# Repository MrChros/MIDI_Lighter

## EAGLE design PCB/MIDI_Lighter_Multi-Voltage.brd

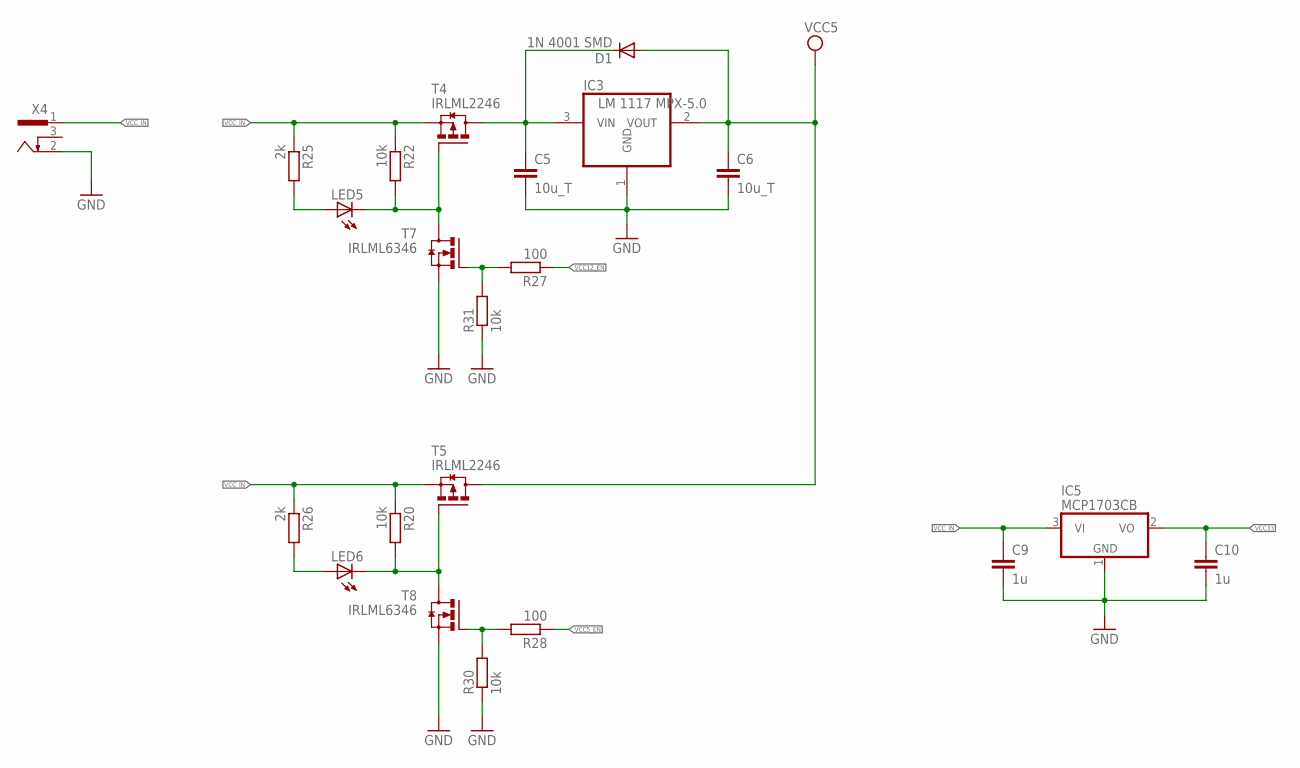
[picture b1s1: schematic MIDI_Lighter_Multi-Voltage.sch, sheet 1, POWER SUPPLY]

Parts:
C5, C6: 10u_T; C1210
C9, C10: 1u; C0805
D1: 1N 4001 SMD; MINIMELF
IC3: LM 1117 MPX-5.0; SOT223
IC5: MCP1703CB; SOT23
LED5, LED6: LEDCHIP-LED0805; CHIP-LED0805
R20, R22, R30, R31: 10k; R0805
R25, R26: 2k; R0805
R27, R28: 100; R0805
T4, T5: IRLML2246; SOT23
T7, T8: IRLML6346; SOT23
X4: 733980-62

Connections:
GND: C5.2, C6.2, C9.2, C10.2, IC3.1 (GND), IC5.1 (GND), R30.1, R31.1, T7.2 (S), T8.2 (S), X4.2; also elsewhere on the board
unnamed: C5.1, D1.C, IC3.3 (VIN), T4.3 (D)
unnamed: LED5.C, R22.2, T4.1 (G), T7.3 (D)
unnamed: LED6.C, R20.2, T5.1 (G), T8.3 (D)
unnamed: LED6.A, R26.2
unnamed: LED5.A, R25.2
unnamed: R27.2, R31.2, T7.1 (G)
unnamed: R28.2, R30.2, T8.1 (G)
VCC: C6.1, D1.A, IC3.2 (VOUT), T5.3 (D); also elsewhere on the board
VCC5_EN: R28.1; also elsewhere on the board
VCC12_EN: R27.1; also elsewhere on the board
VCC33: C10.1, IC5.2 (VO); also elsewhere on the board
VCC_IN: C9.1, IC5.3 (VI), R20.1, R22.1, R25.1, R26.1, T4.2 (S), T5.2 (S), X4.1; also elsewhere on the board

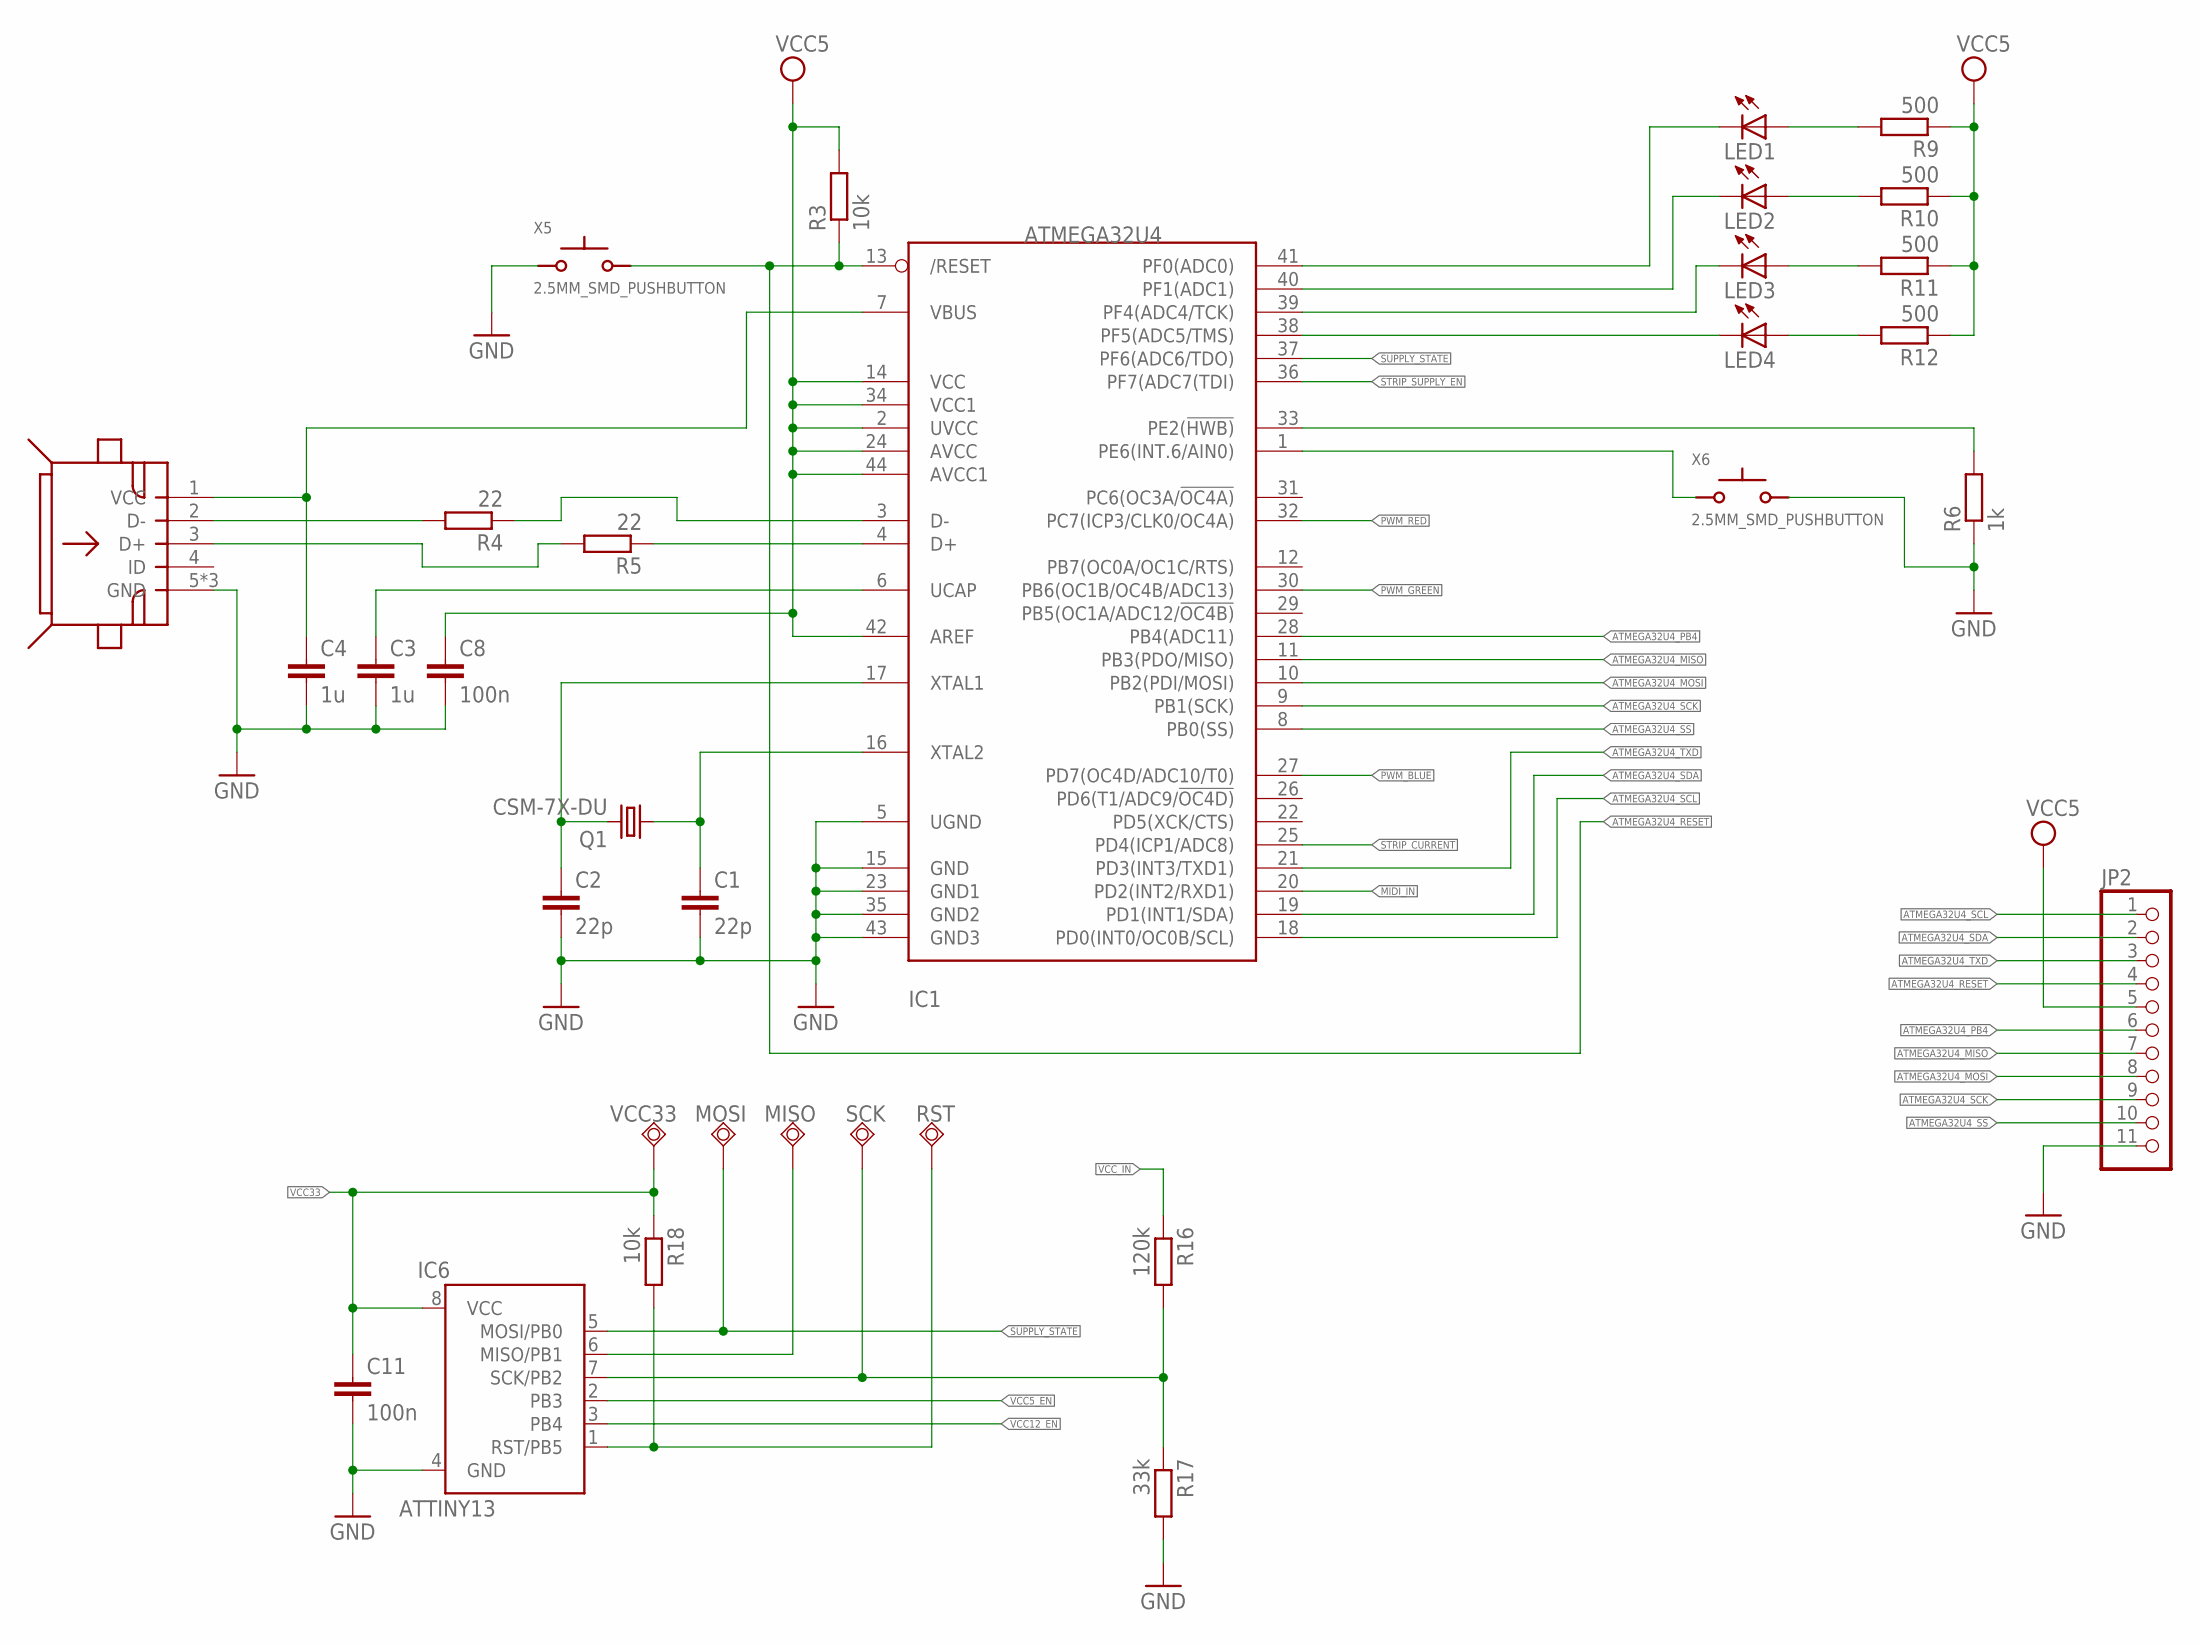
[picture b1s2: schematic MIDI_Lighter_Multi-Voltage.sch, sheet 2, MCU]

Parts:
C1, C2: 22p; C0805
C3, C4: 1u; C0805
C8, C11: 100n; C0805
IC1: ATMEGA32U4; TQFP44
IC6: ATTINY13; SO08
JP2: PINHD-1X11; 1X11
LED1, LED2, LED3, LED4: LEDCHIP-LED0805; CHIP-LED0805
MISO: TPSQTP13R; TP13R
MOSI: TPSQTP13R; TP13R
Q1: CSM-7X-DU
R3, R18: 10k; R0805
R4, R5: 22; R0805
R6: 1k; R0805
R9, R10, R11, R12: 500; R0805
R16: 120k; R0805
R17: 33k; R0805
RST: TPSQTP13R; TP13R
SCK: TPSQTP13R; TP13R
VCC33: TPSQTP13R; TP13R
X3: USB_MICRO_BUCHSE_LCSC
X5, X6: 2.5MM_SMD_PUSHBUTTON

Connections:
ATMEGA32U4_MISO: IC1.11 (PB3(PDO/MISO)), JP2.7
ATMEGA32U4_MOSI: IC1.10 (PB2(PDI/MOSI)), JP2.8; also elsewhere on the board
ATMEGA32U4_PB4: IC1.28 (PB4(ADC11)), JP2.6
ATMEGA32U4_RESET: IC1.13 (/RESET), JP2.4, R3.1, X5.2
ATMEGA32U4_SCK: IC1.9 (PB1(SCK)), JP2.9; also elsewhere on the board
ATMEGA32U4_SCL: IC1.18 (PD0(INT0/OC0B/SCL)), JP2.1
ATMEGA32U4_SDA: IC1.19 (PD1(INT1/SDA)), JP2.2
ATMEGA32U4_SS: IC1.8 (PB0(SS)), JP2.10
ATMEGA32U4_TXD: IC1.21 (PD3(INT3/TXD1)), JP2.3
GND: C1.2, C2.2, C3.2, C4.2, C8.2, C11.2, IC1.5 (UGND), IC1.15 (GND), IC1.23 (GND1), IC1.35 (GND2), IC1.43 (GND3), IC6.4 (GND), JP2.11, R6.1, R17.2, X3.5 (GND), X3.GND1 (GND), X3.GND2 (GND), X5.1, X6.2; also elsewhere on the board
MIDI_IN: IC1.20 (PD2(INT2/RXD1)); also elsewhere on the board
unnamed: R4.2, X3.2 (D-)
unnamed: IC1.3 (D-), R4.1
unnamed: C1.1, IC1.16 (XTAL2), Q1.1
unnamed: C2.1, IC1.17 (XTAL1), Q1.2
unnamed: C3.1, IC1.6 (UCAP)
unnamed: R5.2, X3.3 (D+)
unnamed: IC1.4 (D+), R5.1
unnamed: IC1.33 (PE2(!HWB)), R6.2
unnamed: IC1.41 (PF0(ADC0)), LED1.C
unnamed: IC1.40 (PF1(ADC1)), LED2.C
unnamed: IC1.39 (PF4(ADC4/TCK)), LED3.C
unnamed: IC1.38 (PF5(ADC5/TMS)), LED4.C
unnamed: IC1.1 (PE6(INT.6/AIN0)), X6.1
unnamed: LED1.A, R9.2
unnamed: LED2.A, R10.2
unnamed: LED3.A, R11.2
unnamed: LED4.A, R12.2
unnamed: IC6.1 (RST/PB5), R18.2, RST.TP
unnamed: IC6.6 (MISO/PB1), MISO.TP
PWM_BLUE: IC1.27 (PD7(OC4D/ADC10/T0)); also elsewhere on the board
PWM_GREEN: IC1.30 (PB6(OC1B/OC4B/ADC13)); also elsewhere on the board
PWM_RED: IC1.32 (PC7(ICP3/CLK0/OC4A)); also elsewhere on the board
STRIP_CURRENT: IC1.25 (PD4(ICP1/ADC8)); also elsewhere on the board
STRIP_SUPPLY_EN: IC1.36 (PF7(ADC7(TDI)); also elsewhere on the board
SUPPLY_STATE: IC1.37 (PF6(ADC6/TDO)), IC6.5 (MOSI/PB0), MOSI.TP
VCC: C8.1, IC1.2 (UVCC), IC1.14 (VCC), IC1.24 (AVCC), IC1.34 (VCC1), IC1.42 (AREF), IC1.44 (AVCC1), JP2.5, R3.2, R9.1, R10.1, R11.1, R12.1; also elsewhere on the board
VCC5_EN: IC6.2 (PB3); also elsewhere on the board
VCC12_EN: IC6.3 (PB4); also elsewhere on the board
VCC33: C11.1, IC6.8 (VCC), R18.1, VCC33.TP; also elsewhere on the board
VCC_IN: R16.1; also elsewhere on the board
VCC_USB: C4.1, IC1.7 (VBUS), X3.1 (VCC)
VOLTAGE_READ: IC6.7 (SCK/PB2), R16.2, R17.1, SCK.TP

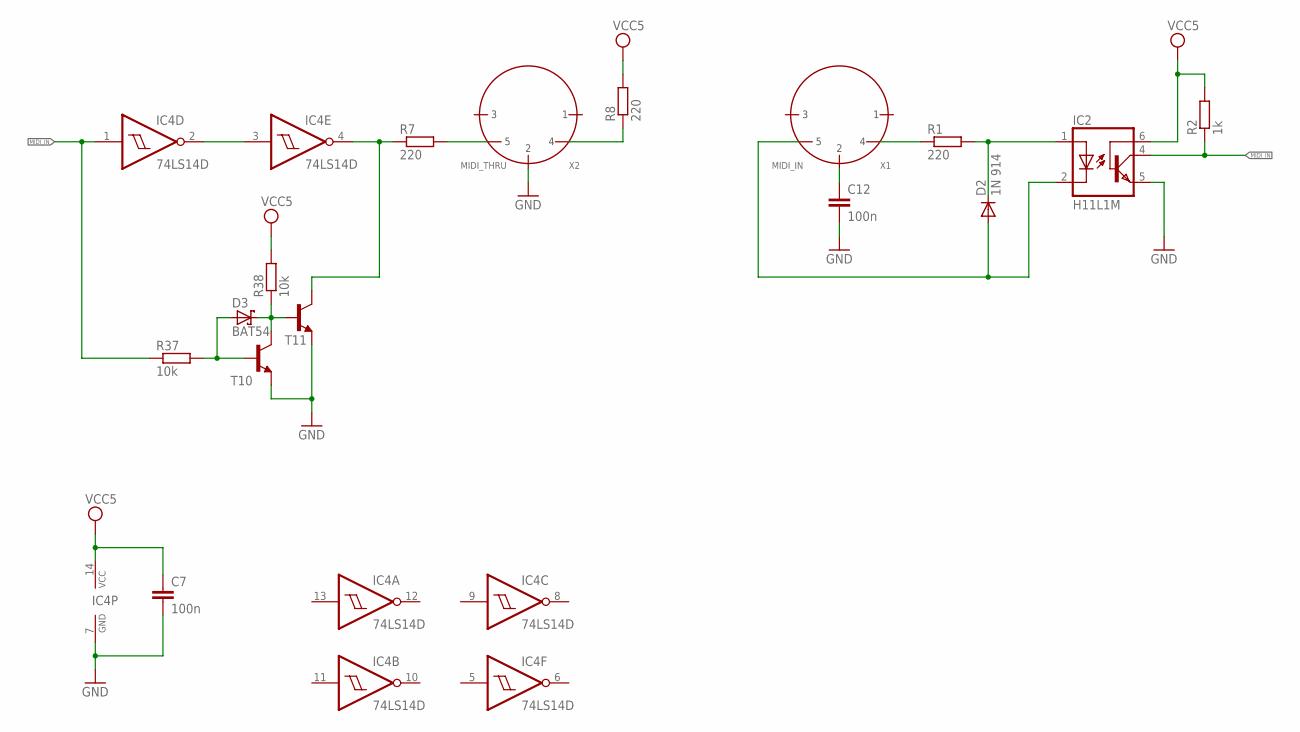
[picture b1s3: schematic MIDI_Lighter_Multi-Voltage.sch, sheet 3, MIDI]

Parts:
C7, C12: 100n; C0805
D2: 1N 914; DO35-10
D3: BAT54; SOT23
IC2: H11L1M; DIL06
IC4: 74LS14D; SO14
R1, R7, R8: 220; R0805
R2: 1k; R0805
R37, R38: 10k; R0805
T10, T11: BC847CLT1-NPN-SOT23-BEC; SOT23-BEC
X1: MIDI_IN; DIN_PLUG_5_PINS
X2: MIDI_THRU; DIN_PLUG_5_PINS

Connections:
GND: C7.2, C12.2, IC2.5 (GND), IC4.7 (GND), T10.E, T11.E, X2.2; also elsewhere on the board
MIDI_IN: IC2.4 (VO), IC4.1 (I), R2.1, R37.1; also elsewhere on the board
unnamed: D2.C, IC2.1 (A), R1.2
unnamed: R1.1, X1.4
unnamed: D2.A, IC2.2 (C), X1.5
unnamed: IC4.2 (O), IC4.3 (I)
unnamed: R7.2, X2.5
unnamed: R8.1, X2.4
unnamed: C12.1, X1.2
unnamed: D3.1 (A), R37.2, T10.B
unnamed: D3.3 (C), R38.1, T10.C, T11.B
unnamed: IC4.4 (O), R7.1, T11.C
VCC: C7.1, IC2.6 (VCC), IC4.14 (VCC), R2.2, R8.2, R38.2; also elsewhere on the board

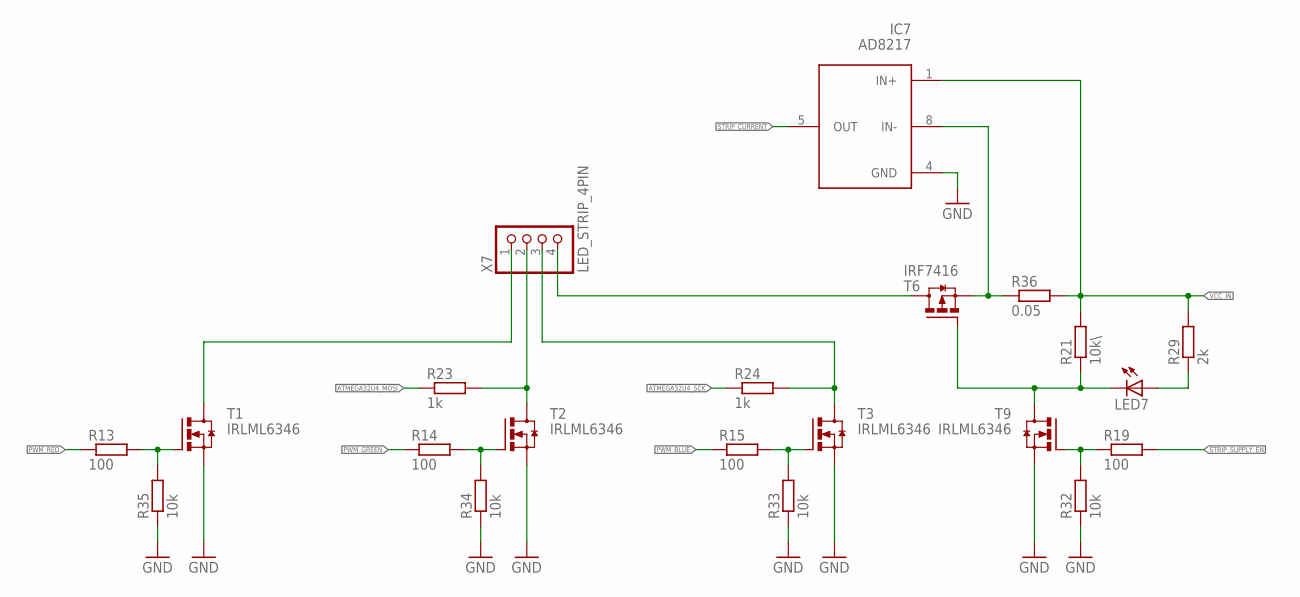
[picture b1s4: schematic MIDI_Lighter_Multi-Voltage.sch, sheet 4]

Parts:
IC7: AD8217; SO08
LED7: LEDCHIP-LED0805; CHIP-LED0805
R13, R14, R15, R19: 100; R0805
R21: 10k\; R0805
R23, R24: 1k; R0805
R29: 2k; R0805
R32, R33, R34, R35: 10k; R0805
R36: 0.05; R2512
T1, T2, T3, T9: IRLML6346; SOT23
T6: IRF7416; SO08
X7: LED_STRIP_4PIN

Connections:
ATMEGA32U4_MOSI: R23.1; also elsewhere on the board
ATMEGA32U4_SCK: R24.1; also elsewhere on the board
GND: IC7.4 (GND), R32.1, R33.1, R34.1, R35.1, T1.2 (S), T2.2 (S), T3.2 (S), T9.2 (S); also elsewhere on the board
unnamed: R13.2, R35.2, T1.1 (G)
unnamed: R14.2, R34.2, T2.1 (G)
unnamed: R15.2, R33.2, T3.1 (G)
unnamed: R23.2, T2.3 (D), X7.2
unnamed: T1.3 (D), X7.1
unnamed: R24.2, T3.3 (D), X7.3
unnamed: T6.5 (D), T6.6 (D), T6.7 (D), T6.8 (D), X7.4
unnamed: LED7.C, R21.1, T6.4 (G), T9.3 (D)
unnamed: R19.1, R32.2, T9.1 (G)
unnamed: LED7.A, R29.1
unnamed: IC7.8 (IN-), R36.1, T6.1 (S), T6.2 (S), T6.3 (S)
PWM_BLUE: R15.1; also elsewhere on the board
PWM_GREEN: R14.1; also elsewhere on the board
PWM_RED: R13.1; also elsewhere on the board
STRIP_CURRENT: IC7.5 (OUT); also elsewhere on the board
STRIP_SUPPLY_EN: R19.2; also elsewhere on the board
VCC_IN: IC7.1 (IN+), R21.2, R29.2, R36.2; also elsewhere on the board

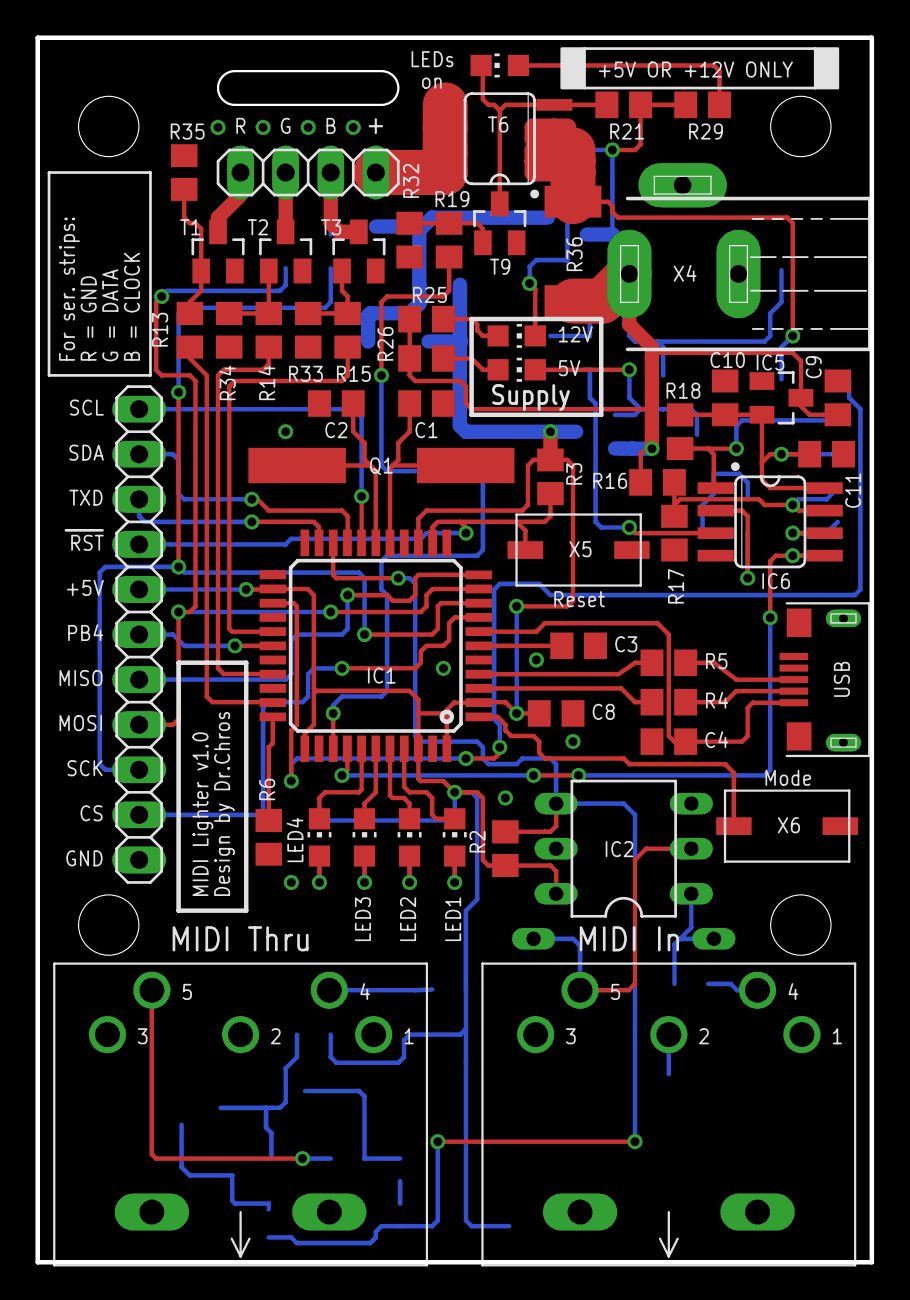
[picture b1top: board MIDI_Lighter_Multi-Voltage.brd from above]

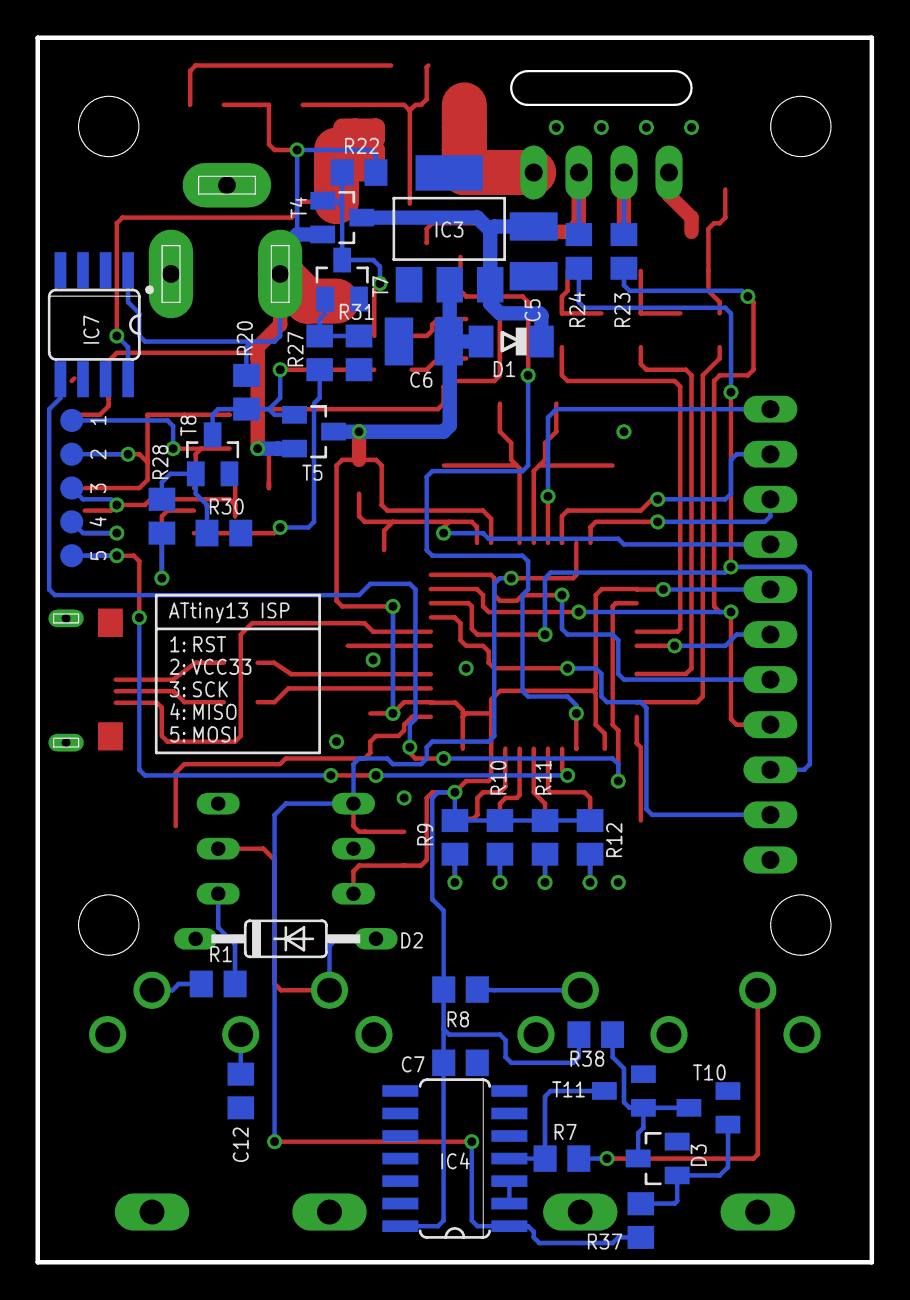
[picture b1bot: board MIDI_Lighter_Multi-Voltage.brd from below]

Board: 2 copper layers, 47.0 x 69.0 mm, 92 parts (38 on the bottom side), 71 nets.

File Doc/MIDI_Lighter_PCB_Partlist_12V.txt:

Partlist

Exported from MIDI_Lighter_12V_Only.sch at 10/07/2018 18:21

EAGLE Version 7.6.0 Copyright (c) 1988-2016 CadSoft

Assembly variant: 

Part     Value                 Device                  Package               Library    Sheet

C1       22p                   C-EUC0805               C0805                 resistor   2
C2       22p                   C-EUC0805               C0805                 resistor   2
C3       1u                    C-EUC0805               C0805                 resistor   2
C4       1u                    C-EUC0805               C0805                 resistor   2
C5       10u_T                 C-EUC1210               C1210                 resistor   1
C6       10u_T                 C-EUC1210               C1210                 resistor   1
C7       100n                  C-EUC0805               C0805                 resistor   3
C8       100n                  C-EUC0805               C0805                 resistor   2
C12      100n                  C-EUC0805               C0805                 resistor   3
D1       1N 4001 SMD           DIODE-MINIMELF          MINIMELF              diode      1
D2       1N 914                DIODE-DO35-10           DO35-10               diode      3
D3       BAT54                 BAT54                   SOT23                 diode      3
IC1      ATMEGA32U4            ATMEGA32U4              TQFP44                ChrosLib   2
IC2      H11L1M                H11L1M                  DIL06                 ChrosLib   3
IC3      LM 1117 MPX-5.0       REG1117                 SOT223                burr-brown 1
IC4      74LS14D               74LS14D                 SO14                  74xx-eu    3
IC7      AD8217                AD8217                  SO08                  ChrosLib   4
JP2                            PINHD-1X11              1X11                  pinhead    2
LED1                           LEDCHIP-LED0805         CHIP-LED0805          led        2
LED2                           LEDCHIP-LED0805         CHIP-LED0805          led        2
LED3                           LEDCHIP-LED0805         CHIP-LED0805          led        2
LED4                           LEDCHIP-LED0805         CHIP-LED0805          led        2
LED7                           LEDCHIP-LED0805         CHIP-LED0805          led        4
Q1       CSM-7X-DU             CSM-7X-DU               CSM-7X-DU             crystal    2
R1       220                   R-EU_R0805              R0805                 resistor   3
R2       1k                    R-EU_R0805              R0805                 resistor   3
R3       10k                   R-EU_R0805              R0805                 resistor   2
R4       22                    R-EU_R0805              R0805                 resistor   2
R5       22                    R-EU_R0805              R0805                 resistor   2
R6       1k                    R-EU_R0805              R0805                 resistor   2
R7       220                   R-EU_R0805              R0805                 resistor   3
R8       220                   R-EU_R0805              R0805                 resistor   3
R9       500                   R-EU_R0805              R0805                 resistor   2
R10      500                   R-EU_R0805              R0805                 resistor   2
R11      500                   R-EU_R0805              R0805                 resistor   2
R12      500                   R-EU_R0805              R0805                 resistor   2
R13      100                   R-EU_R0805              R0805                 resistor   4
R14      100                   R-EU_R0805              R0805                 resistor   4
R15      100                   R-EU_R0805              R0805                 resistor   4
R19      100                   R-EU_R0805              R0805                 resistor   4
R21      10k\                  R-EU_R0805              R0805                 resistor   4
R29      2k                    R-EU_R0805              R0805                 resistor   4
R32      10k                   R-EU_R0805              R0805                 resistor   4
R33      10k                   R-EU_R0805              R0805                 resistor   4
R34      10k                   R-EU_R0805              R0805                 resistor   4
R35      10k                   R-EU_R0805              R0805                 resistor   4
R36      0.05                  R-EU_R2512              R2512                 resistor   4
R37      10k                   R-EU_R0805              R0805                 resistor   3
R38      10k                   R-EU_R0805              R0805                 resistor   3
T1       IRLML6346             IRLML6346               SOT23                 ChrosLib   4
T2       IRLML6346             IRLML6346               SOT23                 ChrosLib   4
T3       IRLML6346             IRLML6346               SOT23                 ChrosLib   4
T6       IRF7416               IRF7416                 SO08                  ChrosLib   4
T9       IRLML6346             IRLML6346               SOT23                 ChrosLib   4
T10                            BC847CLT1-NPN-SOT23-BEC SOT23-BEC             transistor 3
T11                            BC847CLT1-NPN-SOT23-BEC SOT23-BEC             transistor 3
X1       MIDI_IN               DIN_PLUG_5_PINS         DIN_PLUG_5_PINS       ChrosLib   3
X2       MIDI_THRU             DIN_PLUG_5_PINS         DIN_PLUG_5_PINS       ChrosLib   3
X3       USB_MICRO_BUCHSE_LCSC USB_MICRO_BUCHSE_LCSC   USB_MICRO_BUCHSE_LCSC ChrosLib   2
X4                             733980-62               733980-62             con-conrad 1
X5       2.5MM_SMD_PUSHBUTTON  2.5MM_SMD_PUSHBUTTON    2.5MM_SMD_PUSHBUTTON  ChrosLib   2
X6       2.5MM_SMD_PUSHBUTTON  2.5MM_SMD_PUSHBUTTON    2.5MM_SMD_PUSHBUTTON  ChrosLib   2
X7       LED_STRIP_4PIN        LED_STRIP_4PIN          LED_STRIP_4PIN        ChrosLib   4

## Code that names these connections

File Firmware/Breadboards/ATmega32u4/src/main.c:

#define F_CPU	16000000UL

//////////////
// INCLUDES //
//////////////
#include <avr/io.h>
#include <avr/interrupt.h>
#include <util/delay.h>
#include <util/atomic.h>

#include "USB.h"
#include "UART.h"
#include "Timer_and_Button.h"


/////////////
// DEFINES //
/////////////
#define FALSE	0
#define TRUE	1


//////////////////////////////
// Clock Defines
#define CPU_PRESCALE(n) (CLKPR = 0x80, CLKPR = (n))
#define CPU_16MHz       0x00
#define CPU_8MHz        0x01
#define CPU_4MHz        0x02
#define CPU_2MHz        0x03
#define CPU_1MHz        0x04
#define CPU_500kHz      0x05
#define CPU_250kHz      0x06
#define CPU_125kHz      0x07
#define CPU_62kHz       0x08

//////////////////////////////
// LED Defines
#define LED0_PORT	PORTF
#define LED1_PORT	PORTF
#define LED2_PORT	PORTB
#define LEDON_PORT	PORTD

#define LED0_PIN	PF6
#define LED1_PIN	PF7
#define LED2_PIN	PB6
#define LEDON_PIN	PD6

#define LED_ON( _PORT_, _PIN_)		_PORT_ &= ~(1 << _PIN_)
#define LED_OFF( _PORT_, _PIN_)		_PORT_ |= (1 << _PIN_)
#define LED_TOGGLE( _PORT_, _PIN_)	_PORT_ ^= _BV(_PIN_)

//////////////////////////////
// UART Defines
#define UART_CONST_STRING( _str_ )	UART_Send_String( _str_ , sizeof( _str_ )-1)

//////////////////////////////
// LED Defines
#define NUMBER_OF_LEDS			60
#define RED						0
#define GREEN					1
#define BLUE					2
#define UNDEFINED				255

#define CONSTANT_RED			255
#define CONSTANT_GREEN			255
#define CONSTANT_BLUE			0

#define TIMEOUT_THRESHOLD		50000
#define NOTE_OFF_TIMEOUT		100


//////////////////////////////
// MIDI Defines
#define MIDI_COMPARE_NOTE_OFF	0x8		// Note off
#define	MIDI_COMPARE_NOTE_ON	0x9		// Note on
#define	MIDI_COMPARE_CHANNEL	0x0
#define MIDI_COMAPRE_NOTE_RED	0x24
#define MIDI_COMAPRE_NOTE_GREEN	0x28
#define MIDI_COMAPRE_NOTE_BLUE	0x2C



///////////////
// FUNCTIONS //
///////////////
void	WS2801_Update(void);

///////////////
// VARIABLES //
///////////////
volatile uint8_t	_Color[3];
volatile uint8_t	_Note_Off_Pending[3];
volatile uint32_t	_Note_Off_Counter[3];
volatile uint8_t	_Update_WS2801;
volatile uint8_t	_No_Data_Light_On_Old;
volatile uint8_t	_No_Data_Light_On_Fade_Div;

enum PARSING_STATE_e
{
	WAITING,
	STATUS_AND_CHANNEL_RECEIVED,
	NOTE_RECEIVED
};

enum MODE_e
{
	MIDI,
	CONSTANT	
};

struct PARSING_s
{
	enum PARSING_STATE_e State;
	uint8_t Event;
	uint8_t Color;
};



int main (void)
{
	CPU_PRESCALE(CPU_16MHz);
	
	_Color[RED] 				= 0;
	_Color[GREEN] 				= 0;
	_Color[BLUE] 				= 0;
	
	_Note_Off_Pending[RED]		= FALSE;
	_Note_Off_Pending[GREEN]	= FALSE;
	_Note_Off_Pending[BLUE]		= FALSE;
	
	_Note_Off_Counter[RED]		= 0;
	_Note_Off_Counter[GREEN]	= 0;
	_Note_Off_Counter[BLUE]		= 0;
		
	_Update_WS2801				= FALSE;
	
	_No_Data_Light_On_Old		= FALSE;
	_No_Data_Light_On_Fade_Div	= 0;

	// Configure LEDs
	DDRF |= (1 << PF6) | (1 << PF7);	// Set LED Pins to Output
	DDRB |= (1 << PB6);					// Set LED Pin to Output
	DDRD |= (1 << PD6);

	PORTD |= (1 << PD6);
	
	UART_Init();

	// Initialize SPI @ 4 MHz
	DDRB |= (1 << PB2) | (1 << PB1) | (1 << PB0);	// Set SCK, MOSI and CS to Output
	SPCR  = (1 << SPE) | (1 << MSTR);				// Enable SPI as Master
	
	WS2801_Update();
	
	// Parsing Structure
	struct PARSING_s Parsing;
	Parsing.State = WAITING;
	Parsing.Event = MIDI_COMPARE_NOTE_ON;
	Parsing.Color = UNDEFINED;	
	
	// Timeout Counter
	uint32_t Timeout = 0;
	
	enum MODE_e Mode = MIDI;	
	
	Timer_And_Button_Init();
	
//	USB_Init();
//	_delay_ms(250);
	sei();
	
	LED_OFF(LED0_PORT, LED0_PIN);
	LED_OFF(LED1_PORT, LED1_PIN);
	LED_OFF(LED2_PORT, LED2_PIN);
	
	while(1)
	{
		while(UART_Data_Available()>0)
		{
			uint8_t Data = UART_Buffer_Read();
			
			Timer_No_Data_Light_Reset();
			if(Timer_No_Data_Light_On() == FALSE && _No_Data_Light_On_Old == TRUE)
			{
				_No_Data_Light_On_Old	= Timer_No_Data_Light_On();
				_Color[RED]				= 0;
				_Color[GREEN]			= 0;
				_Color[BLUE]			= 0;
				_Update_WS2801			= TRUE;
			}
			
			if(Mode != MIDI) { continue; }
						
			switch(Parsing.State)
			{
				case WAITING:
					if(((((Data & 0xF0) >> 4) == MIDI_COMPARE_NOTE_ON) | ((((Data & 0xF0) >> 4) == MIDI_COMPARE_NOTE_OFF))) && ((Data & 0x0F) == MIDI_COMPARE_CHANNEL))
					{
						Parsing.State 	= STATUS_AND_CHANNEL_RECEIVED;
						Parsing.Event	= ((Data & 0xF0) >> 4);
						Timeout			= 0;
						LED_ON(LED0_PORT, LED0_PIN);
					}
					break;
				
				case STATUS_AND_CHANNEL_RECEIVED:
					if((Data & 0x80) == 0)
					{
							 if(Data == MIDI_COMAPRE_NOTE_RED	) { Parsing.Color = RED; 	}
						else if(Data == MIDI_COMAPRE_NOTE_GREEN	) { Parsing.Color = GREEN; 	}
						else if(Data == MIDI_COMAPRE_NOTE_BLUE	) { Parsing.Color = BLUE; 	}
						else
						{
							Parsing.State 	= WAITING;
							Parsing.Color	= UNDEFINED;
							Timeout			= 0;
							LED_OFF(LED0_PORT, LED0_PIN);
							LED_OFF(LED1_PORT, LED1_PIN);
							LED_OFF(LED2_PORT, LED2_PIN);
						}
						
						if(Parsing.Color != UNDEFINED)
						{
							Parsing.State 	= NOTE_RECEIVED;
							Timeout			= 0;
							LED_ON(LED1_PORT, LED1_PIN);
						}
					}
					else
					{
						Parsing.State 	= WAITING;
						Parsing.Color	= UNDEFINED;
						Timeout			= 0;
						LED_OFF(LED0_PORT, LED0_PIN);
						LED_OFF(LED1_PORT, LED1_PIN);
						LED_OFF(LED2_PORT, LED2_PIN);
					}
					break;
				
				case NOTE_RECEIVED:
					if((Data & 0x80) == 0)
					{
						if(Parsing.Event == MIDI_COMPARE_NOTE_ON)
						{
							_Color[Parsing.Color] 				= Data << 1;
							_Note_Off_Pending[Parsing.Color]	= FALSE;
						}
						else if(Parsing.Event == MIDI_COMPARE_NOTE_OFF)
						{
							_Note_Off_Pending[Parsing.Color]	= TRUE;
							_Note_Off_Counter[Parsing.Color]	= NOTE_OFF_TIMEOUT;
						}
						
						_Update_WS2801 = TRUE;
						LED_ON(LED2_PORT, LED2_PIN);
					}
					else
					{
						LED_OFF(LED0_PORT, LED0_PIN);
						LED_OFF(LED1_PORT, LED1_PIN);
						LED_OFF(LED2_PORT, LED2_PIN);
					}
					Parsing.State	= WAITING;
					Parsing.Color	= UNDEFINED;
					Timeout			= 0;
					break;
				
				default:
					Parsing.State = WAITING;
					break;
			}
		}
	
		if((Parsing.State == STATUS_AND_CHANNEL_RECEIVED) || (Parsing.State == NOTE_RECEIVED))
		{
			Timeout++;
			
			if(Timeout == TIMEOUT_THRESHOLD)
			{
				Parsing.State 	= WAITING;
				Parsing.Color 	= UNDEFINED;
				
				Timeout = 0;
			}
		}
		
		uint8_t i;
		for(i=RED;i<=BLUE;i++)
		{
			if(_Note_Off_Counter[i]>0)
			{
				_Note_Off_Counter[i]--;
				if(_Note_Off_Counter[i]==0 && _Note_Off_Pending[i]==TRUE)
				{
					_Color[i]				= 0;
					_Note_Off_Pending[i]	= FALSE;
					_Update_WS2801			= TRUE;
				}
			}
		}
		
		if(_Update_WS2801 == TRUE && Timer_WS2801_OV_Occurred() == TRUE)
		{
			_Update_WS2801		= FALSE;
			if(Button_Short_State() == TRUE && _No_Data_Light_On_Old == TRUE)
			{
				if(_No_Data_Light_On_Fade_Div == 3)
				{
					if(_Color[RED]		< CONSTANT_RED	) { _Color[RED]		+= 1; }
					if(_Color[GREEN]	< CONSTANT_GREEN) { _Color[GREEN]	+= 1; }
					if(_Color[BLUE]		< CONSTANT_BLUE	) { _Color[BLUE]	+= 1; }
					
					_No_Data_Light_On_Fade_Div = 0;
				}
				else
				{
					_No_Data_Light_On_Fade_Div++;
				}
			}
			
			WS2801_Update();
		}
		
		if(Button_Short_Pressed() == TRUE)
		{
			uint8_t i;
			for(i=0;i<6;i++)
			{
				LED_TOGGLE(LED0_PORT, LED0_PIN);
				LED_TOGGLE(LED1_PORT, LED1_PIN);
				LED_TOGGLE(LED2_PORT, LED2_PIN);
				_delay_ms(150);
			}
		}
		
		if(Button_Long_Pressed() == TRUE)
		{
			if(Mode == MIDI)
			{
				Mode = CONSTANT;
				
				_Color[RED]		= CONSTANT_RED;
				_Color[GREEN]	= CONSTANT_GREEN;
				_Color[BLUE]	= CONSTANT_BLUE;
				
				_Update_WS2801 = TRUE;
			}
			else if(Mode == CONSTANT)
			{
				Mode = MIDI;
				
				_Color[RED]		= 0;
				_Color[GREEN]	= 0;
				_Color[BLUE]	= 0;
				
				_Update_WS2801 = TRUE;
			}
		}
		
		if(Timer_WS2801_On_LED_Blick() == TRUE)
		{
			if(Button_Short_State() == FALSE)
			{
				LED_OFF(PORTD, PD6);	// In fact, it's turning the LED on
			}
			else
			{
				LED_TOGGLE(PORTD, PD6);
			}
		}
		
		if(Button_Short_State() == TRUE)
		{
			if(Timer_No_Data_Light_On() == TRUE && _No_Data_Light_On_Old == FALSE)
			{
				_Color[RED]				= 0;
				_Color[GREEN]			= 0;
				_Color[BLUE]			= 0;
		
				_No_Data_Light_On_Old	= Timer_No_Data_Light_On();
			}
			
			_Update_WS2801			= TRUE;
		}
		else
		{
			Timer_No_Data_Light_Reset();
		}
		
		_delay_us(10);
	}
}


void WS2801_Update(void)
{
	ATOMIC_BLOCK(ATOMIC_FORCEON)
	{
		uint16_t i;
		
		Timer_WS2801_Restart();
		
		for(i=0;i<NUMBER_OF_LEDS;i++)
		{
			SPDR = _Color[RED];				// Start SPI Transmission
			while(!(SPSR & (1 << SPIF)));	// Wait Transmission complete
		
			SPDR = _Color[BLUE];			// Start SPI Transmission
			while(!(SPSR & (1 << SPIF)));	// Wait Transmission complete
		
			SPDR = _Color[GREEN];			// Start SPI Transmission
			while(!(SPSR & (1 << SPIF)));	// Wait Transmission complete
		}
	
		LED_OFF(LED0_PORT, LED0_PIN);
		LED_OFF(LED1_PORT, LED1_PIN);
		LED_OFF(LED2_PORT, LED2_PIN);
	}
}

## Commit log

2018-09-30 Initial commit of whole MIDI Lighter project
2018-09-30 MIDI Lighter GUI: - Reorganized object structure - Device List now hold the USB Connection - Former Connection-Object removed
2018-09-30 MIDI Lighter GUI: - Name in Device List is updated with name on device itself
2018-09-30 PCB Firmware: - Added initial functions for ADC
2018-10-01 MIDI Lighter GUI: - Restructuring Debug Functions
    Firmware:
    - Added command to read ADC value
    - Seems to work, but AD8217 is not functioning correctly :(
2018-10-05 Firmware: - ADC is working now - Reason for not working current measurement was missing protection at differential input of AD8217 - Two opposite oriented diodes parallel to the shunt resistor solve 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
    Software:
    - Implemented debug interface - not very useful yet, but fits the debugging
    Documents:
    - Added Spep Calculation Sheet for ADC Values
2018-10-05 Documents: - Added image of possible AD8217 input protection
2018-10-07 Firmware: - Added configuration parameter for "No Data Light" - It is now possible to select, when the "No Data Light" shall be switched off
    Software:
    - Updated GUI accordingly with ComboBox to select the new Parameter
2018-10-07 Firmware: - Added basic SPI Library - Added Debug Outputs to MIDI Parsing function
    Documentation:
    - Added Measurements of Skip Note Off function
2018-10-07 Software: - Implemented handling of multiple connected devices - Seems to work and number should be unlimited (tested with only two devices)
2018-10-08 Firmware: - Just removed debug pin declarations in MIDI.c - Added comment to MIDI.c
    Documentation:
    - Added information about random MIDI data sent by Behringer XR18
2018-10-22 Firmware: - Lots of testing with ADC using smart Algorithms - nothing really worked so far - Should be stable now
    GUI:
    - Added a bit fanciness
    - Added release build version (Debug buttons are disabled)
    - Added debug auto test to change PWM frequency and ADC frequency
2018-10-26 Software: - Added first attempts for auto DPI scaling of the Software (not working yet)
2018-11-16 Software: - Added initial structure for strip menu
2022-03-05 Commiting modified changes from a long time ago. I do not recall what changes were made, but the diff shows quite some entries. One of the last things definitely concerned the investigation of the XR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
